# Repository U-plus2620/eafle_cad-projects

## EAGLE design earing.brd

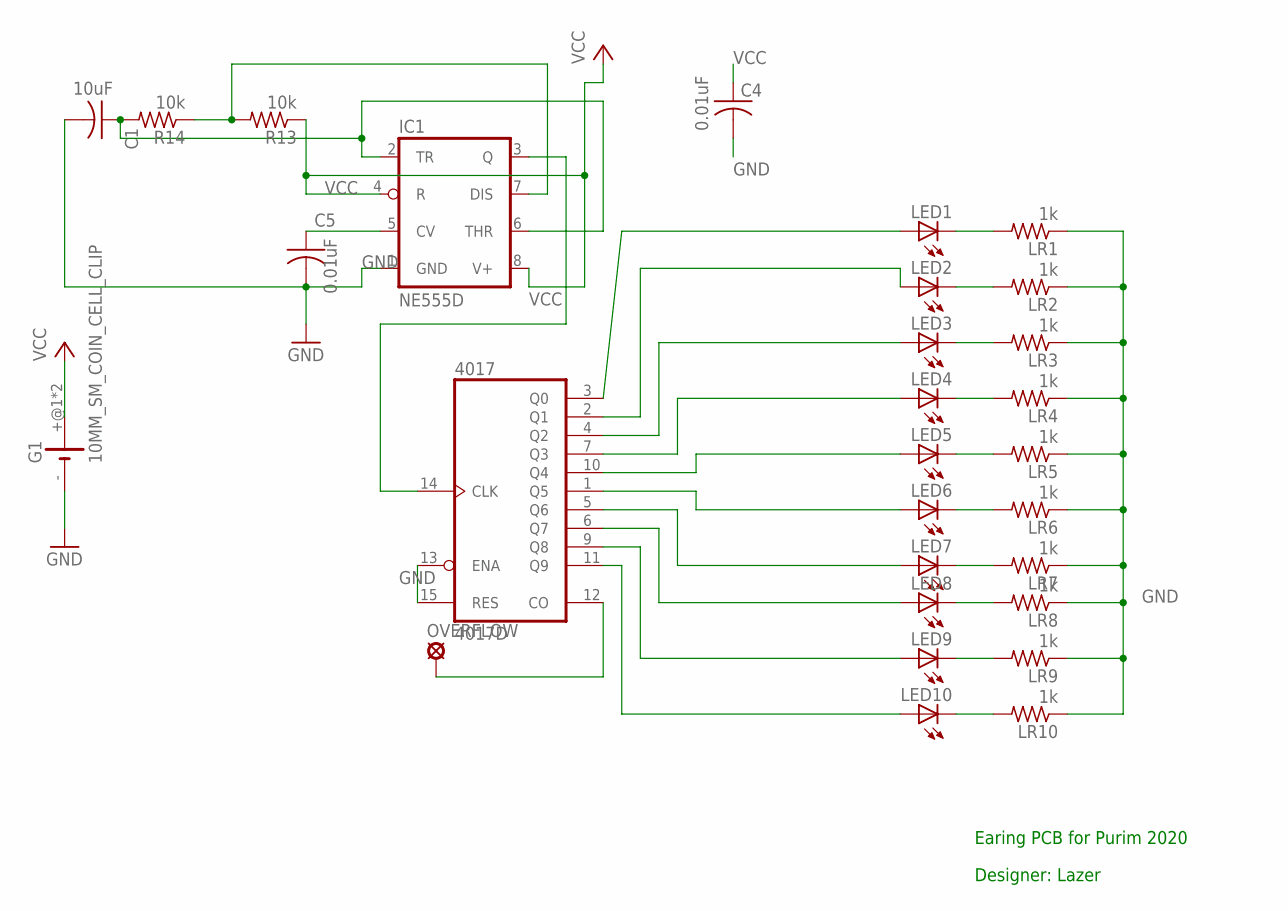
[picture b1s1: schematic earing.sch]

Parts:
4017: 4017D; SO16
C1: 10uF; C0805
C4, C5: 0.01uF; C0805
G1: 10MM_SM_COIN_CELL_CLIP
IC1: NE555D; SO08
LED1, LED2, LED3, LED4, LED5, LED6, LED7, LED8, LED9, LED10: LEDCHIP-LED0805; CHIP-LED0805
LR1, LR2, LR3, LR4, LR5, LR6, LR7, LR8, LR9, LR10: 1k; M0805
OVERFLOW: LSP10
R13, R14: 10k; M0805

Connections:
GND: 4017.13 (ENA), 4017.15 (RES), C1.2, C4.2, C5.2, G1.-, IC1.1 (GND), LR1.1, LR2.1, LR3.1, LR4.1, LR5.1, LR6.1, LR7.1, LR8.1, LR9.1, LR10.1
unnamed: 4017.3 (Q0), LED1.A
unnamed: 4017.12 (CO), OVERFLOW.MP
unnamed: 4017.2 (Q1), LED2.A
unnamed: 4017.4 (Q2), LED3.A
unnamed: 4017.7 (Q3), LED4.A
unnamed: 4017.10 (Q4), LED5.A
unnamed: 4017.1 (Q5), LED6.A
unnamed: 4017.5 (Q6), LED7.A
unnamed: 4017.6 (Q7), LED8.A
unnamed: 4017.9 (Q8), LED9.A
unnamed: 4017.11 (Q9), LED10.A
unnamed: LED10.C, LR10.2
unnamed: LED9.C, LR9.2
unnamed: LED8.C, LR8.2
unnamed: LED7.C, LR7.2
unnamed: LED6.C, LR6.2
unnamed: LED5.C, LR5.2
unnamed: LED4.C, LR4.2
unnamed: LED3.C, LR3.2
unnamed: LED2.C, LR2.2
unnamed: LED1.C, LR1.2
unnamed: C5.1, IC1.5 (CV)
unnamed: IC1.7 (DIS), R13.2, R14.1
unnamed: 4017.14 (CLK), IC1.3 (Q)
unnamed: C1.1, IC1.2 (TR), IC1.6 (THR), R14.2
VCC: 4017.16 (VDD), C4.1, G1.+@1 (+), G1.+@2 (+), IC1.4 (R), IC1.8 (V+), R13.1
VSS: 4017.8 (VSS)

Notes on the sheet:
Earing PCB for Purim 2020
Designer: Lazer

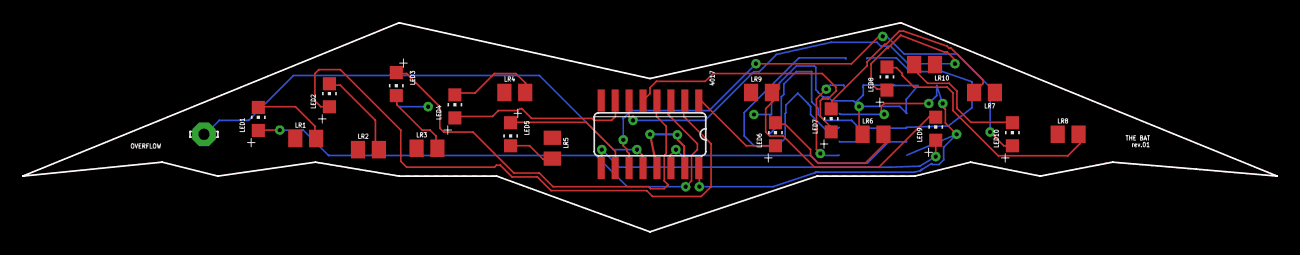
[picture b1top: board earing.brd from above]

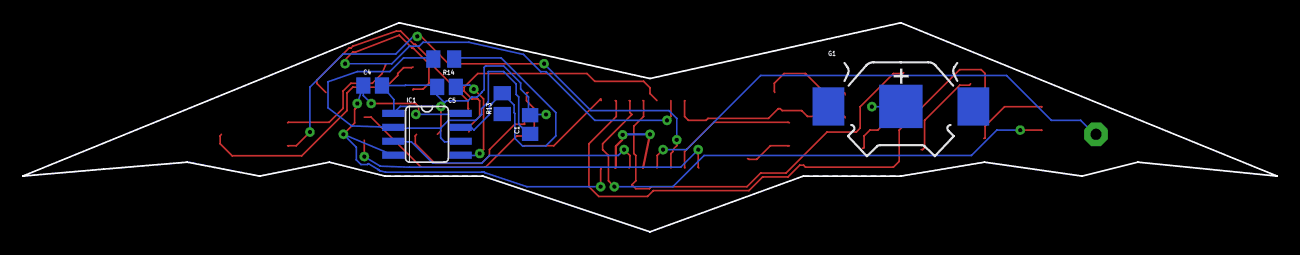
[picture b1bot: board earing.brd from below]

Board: 2 copper layers, 114.3 x 19.1 mm, 29 parts (7 on the bottom side), 27 nets.
